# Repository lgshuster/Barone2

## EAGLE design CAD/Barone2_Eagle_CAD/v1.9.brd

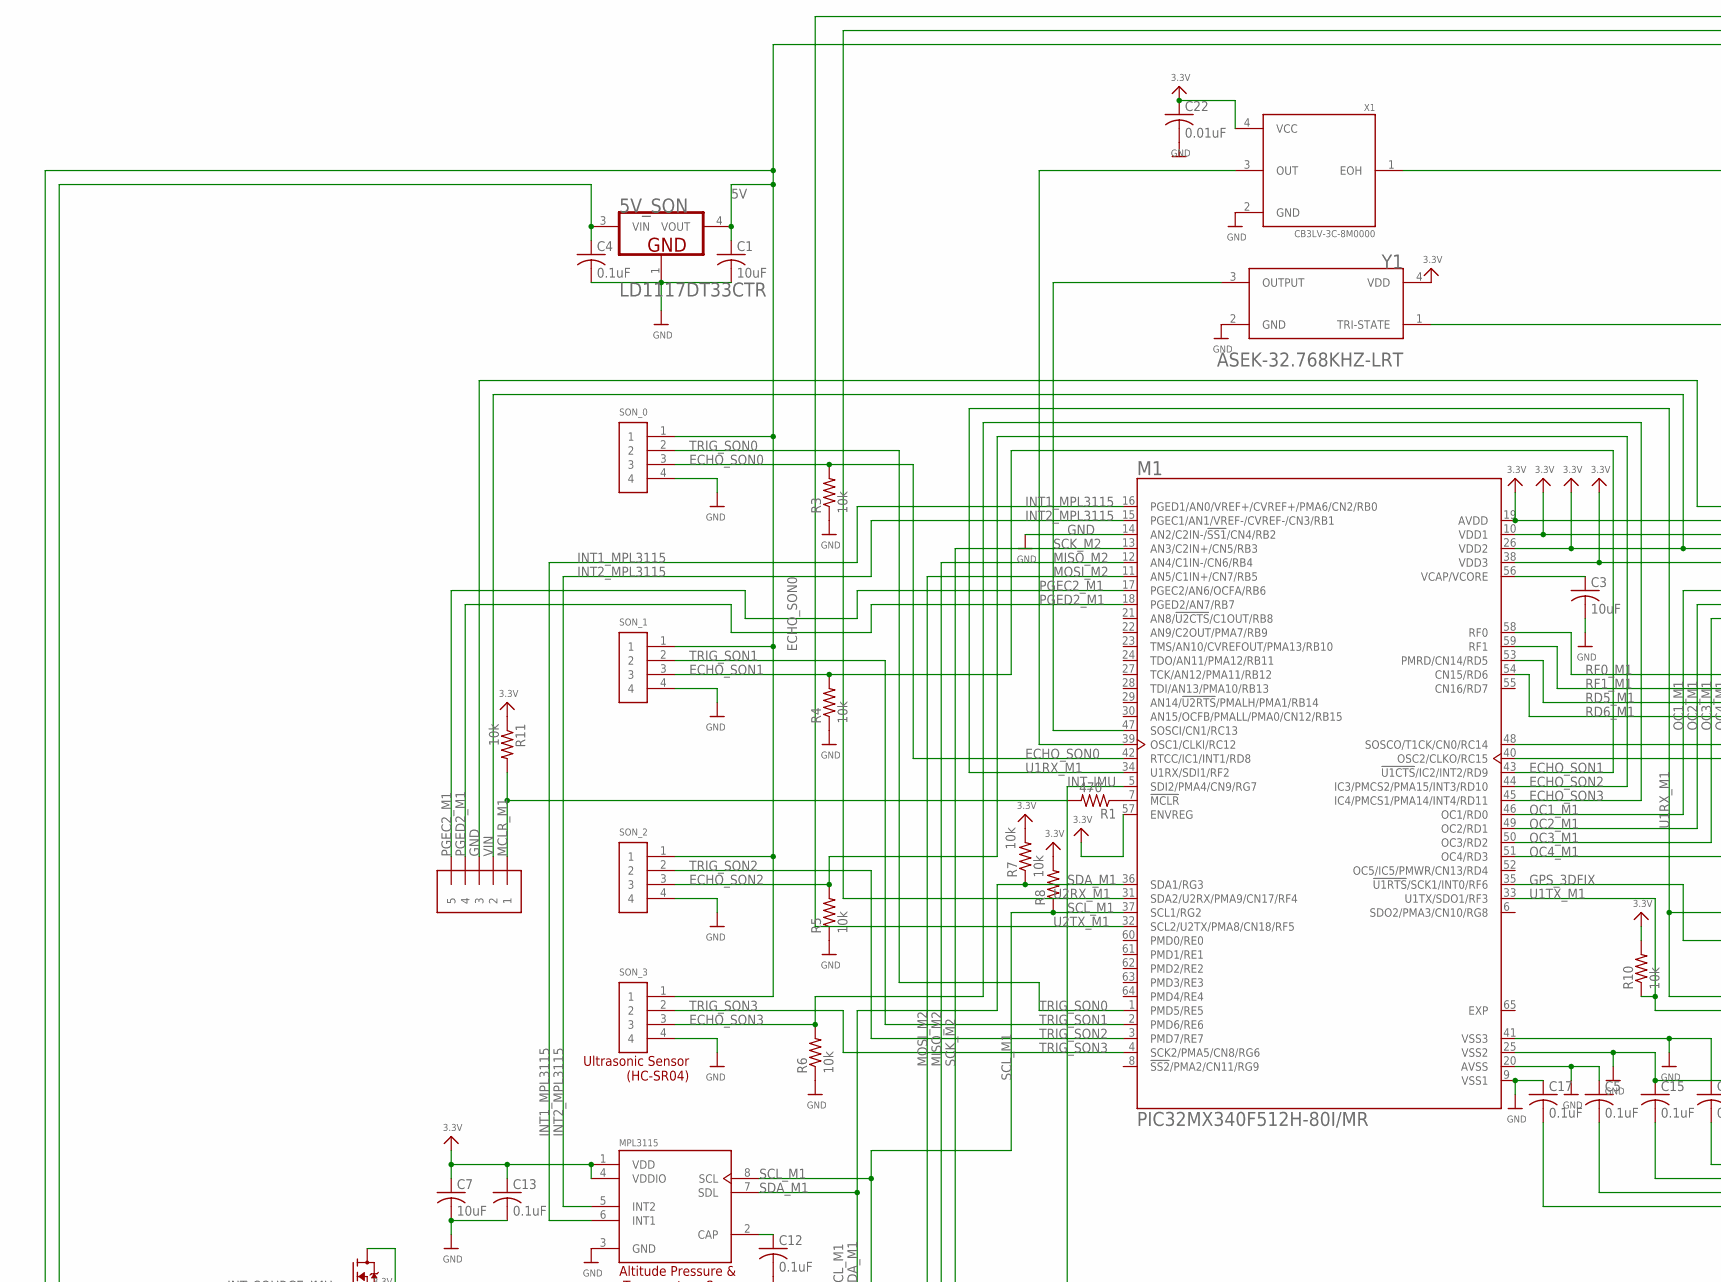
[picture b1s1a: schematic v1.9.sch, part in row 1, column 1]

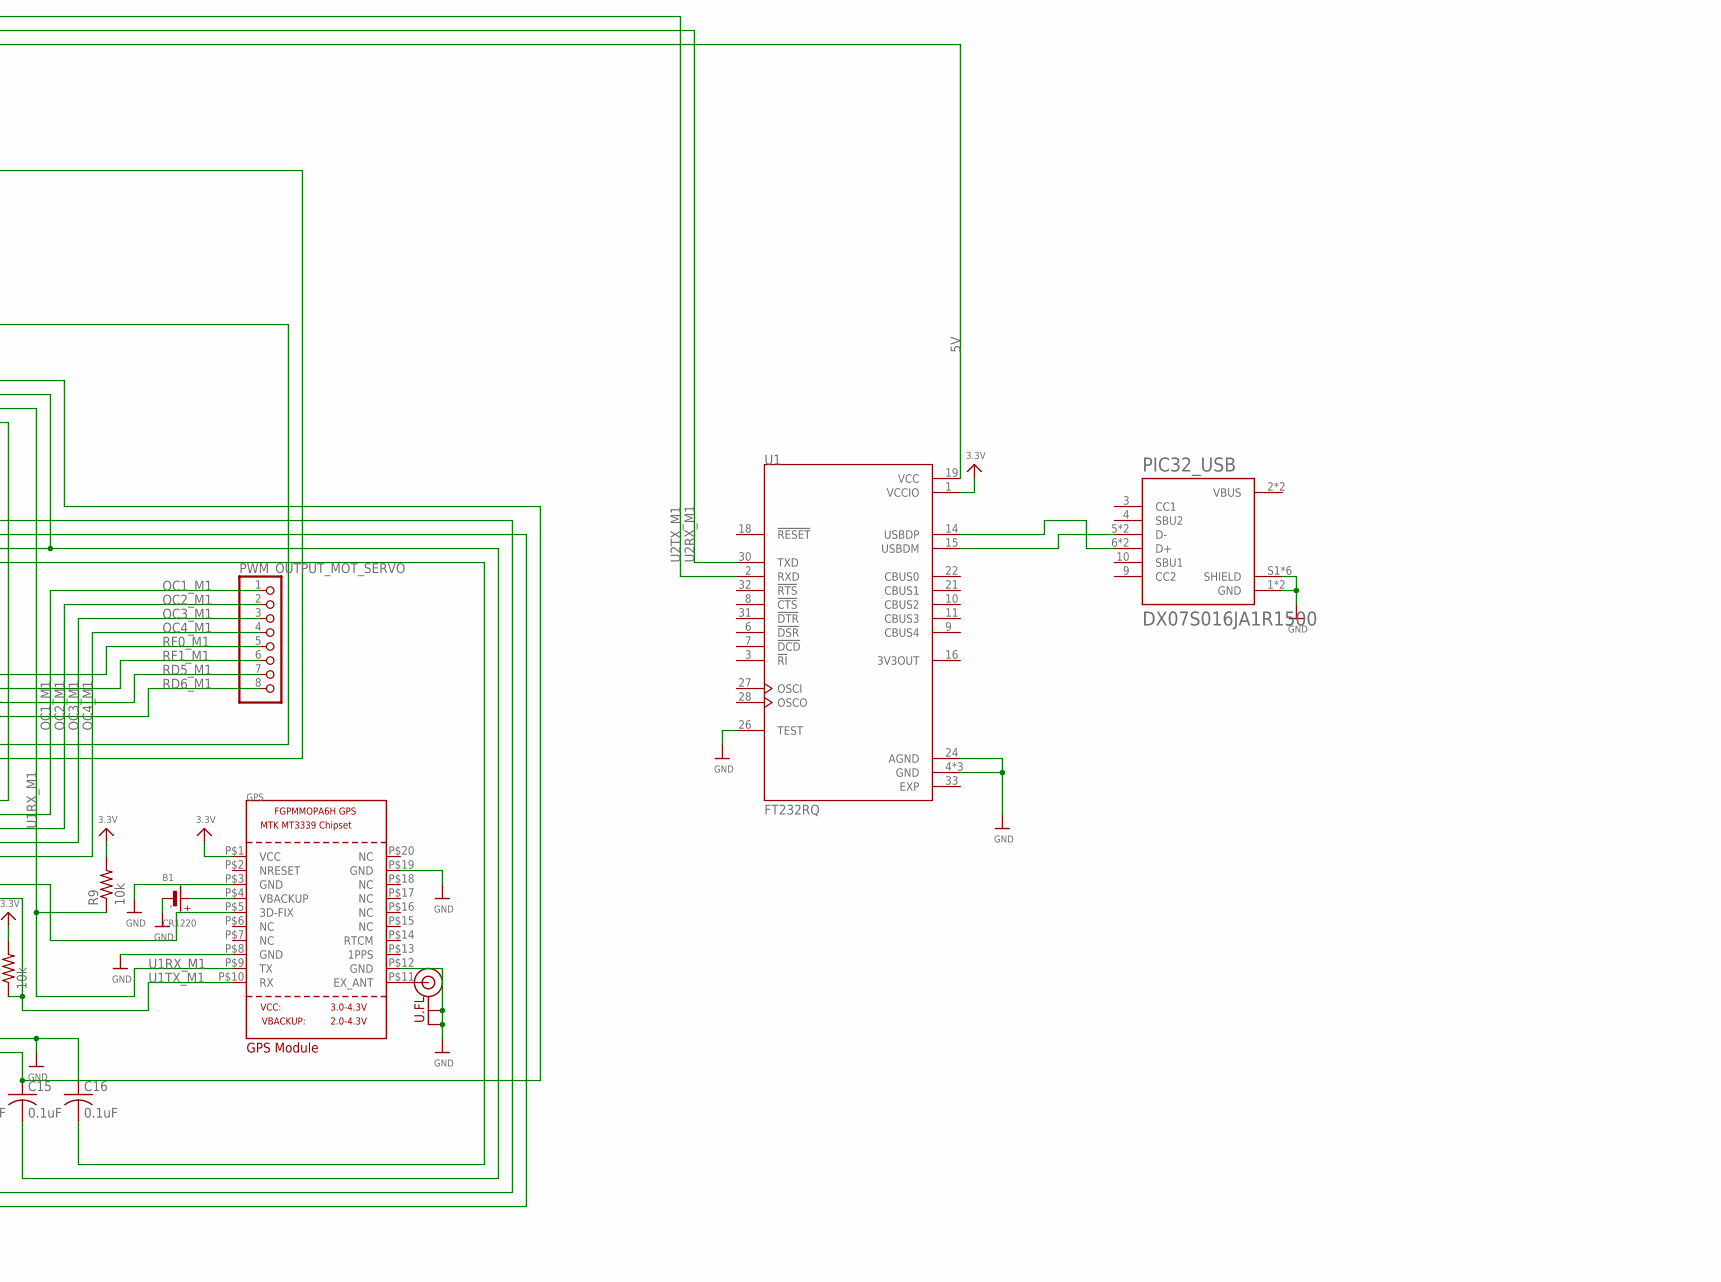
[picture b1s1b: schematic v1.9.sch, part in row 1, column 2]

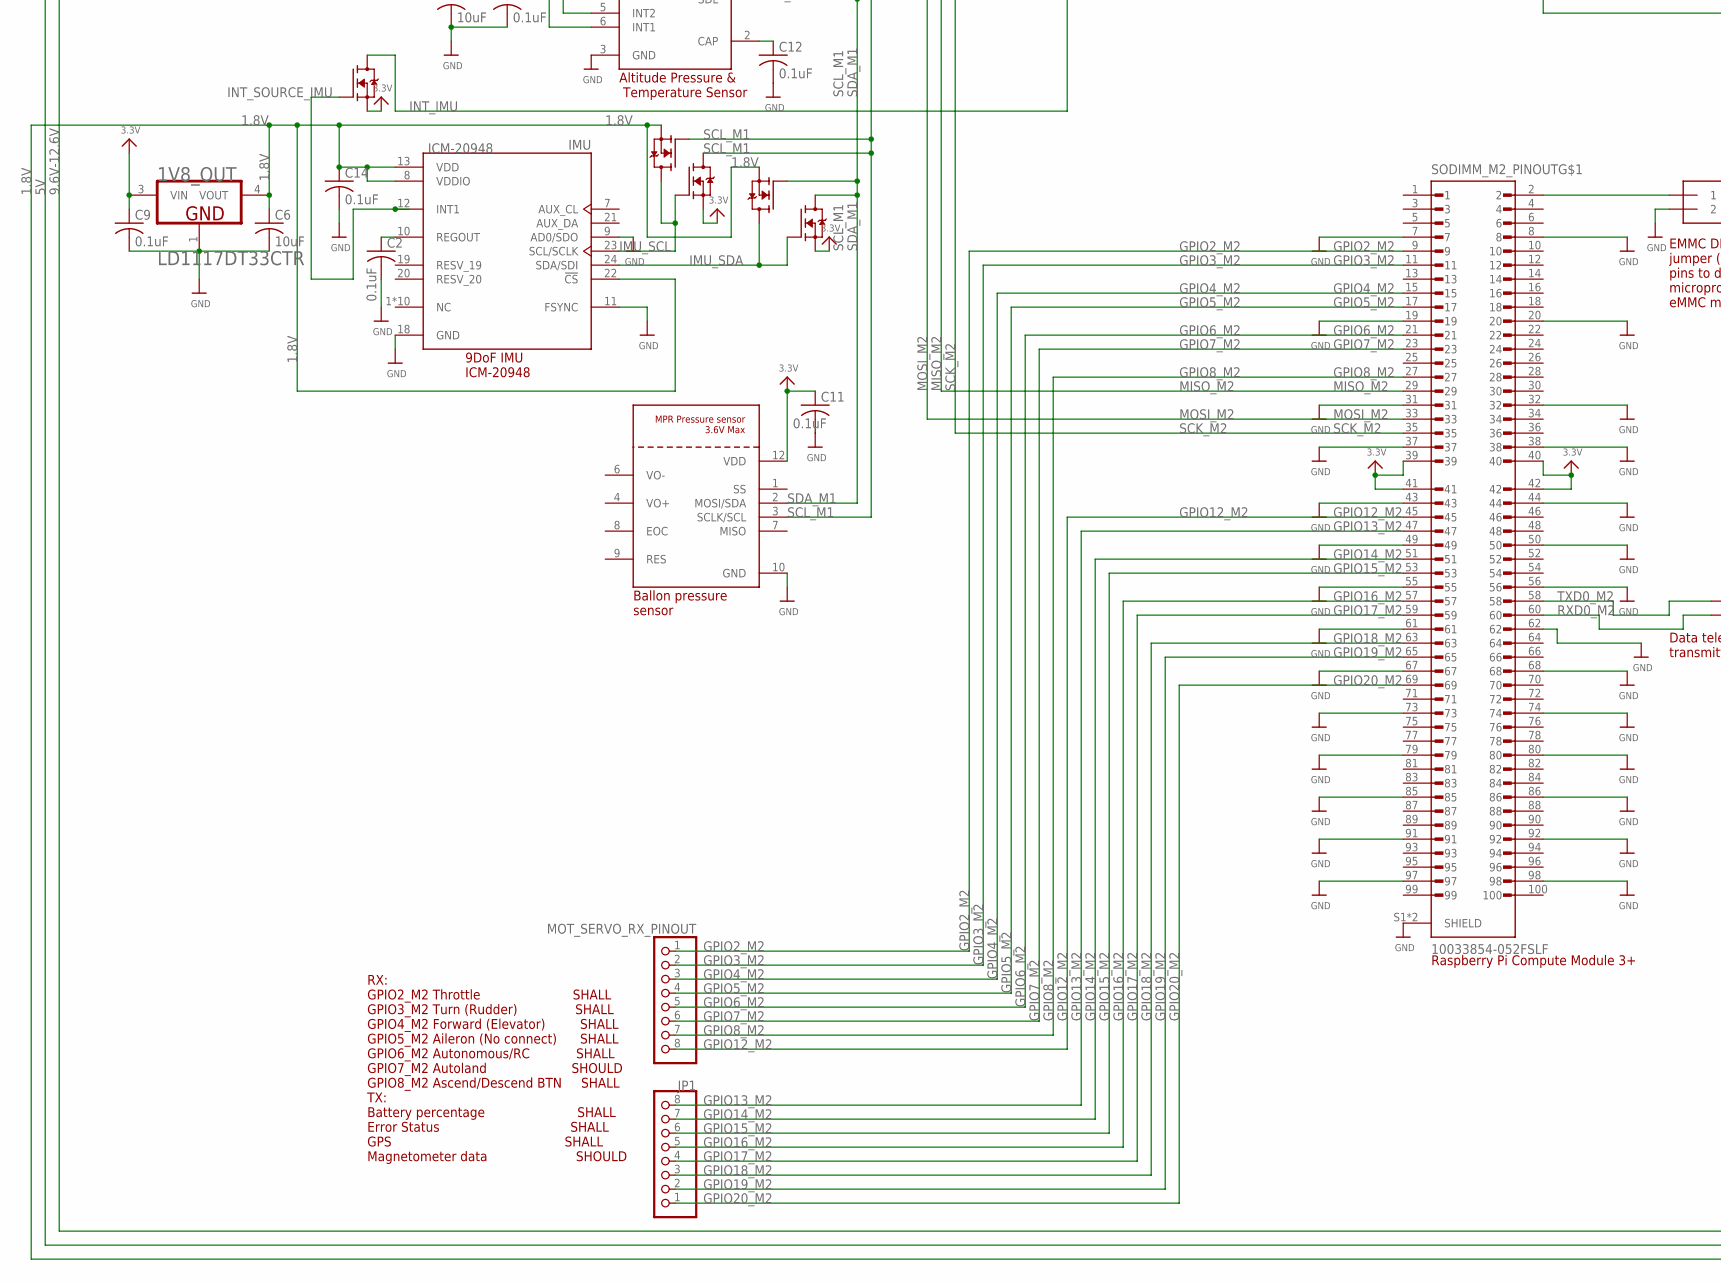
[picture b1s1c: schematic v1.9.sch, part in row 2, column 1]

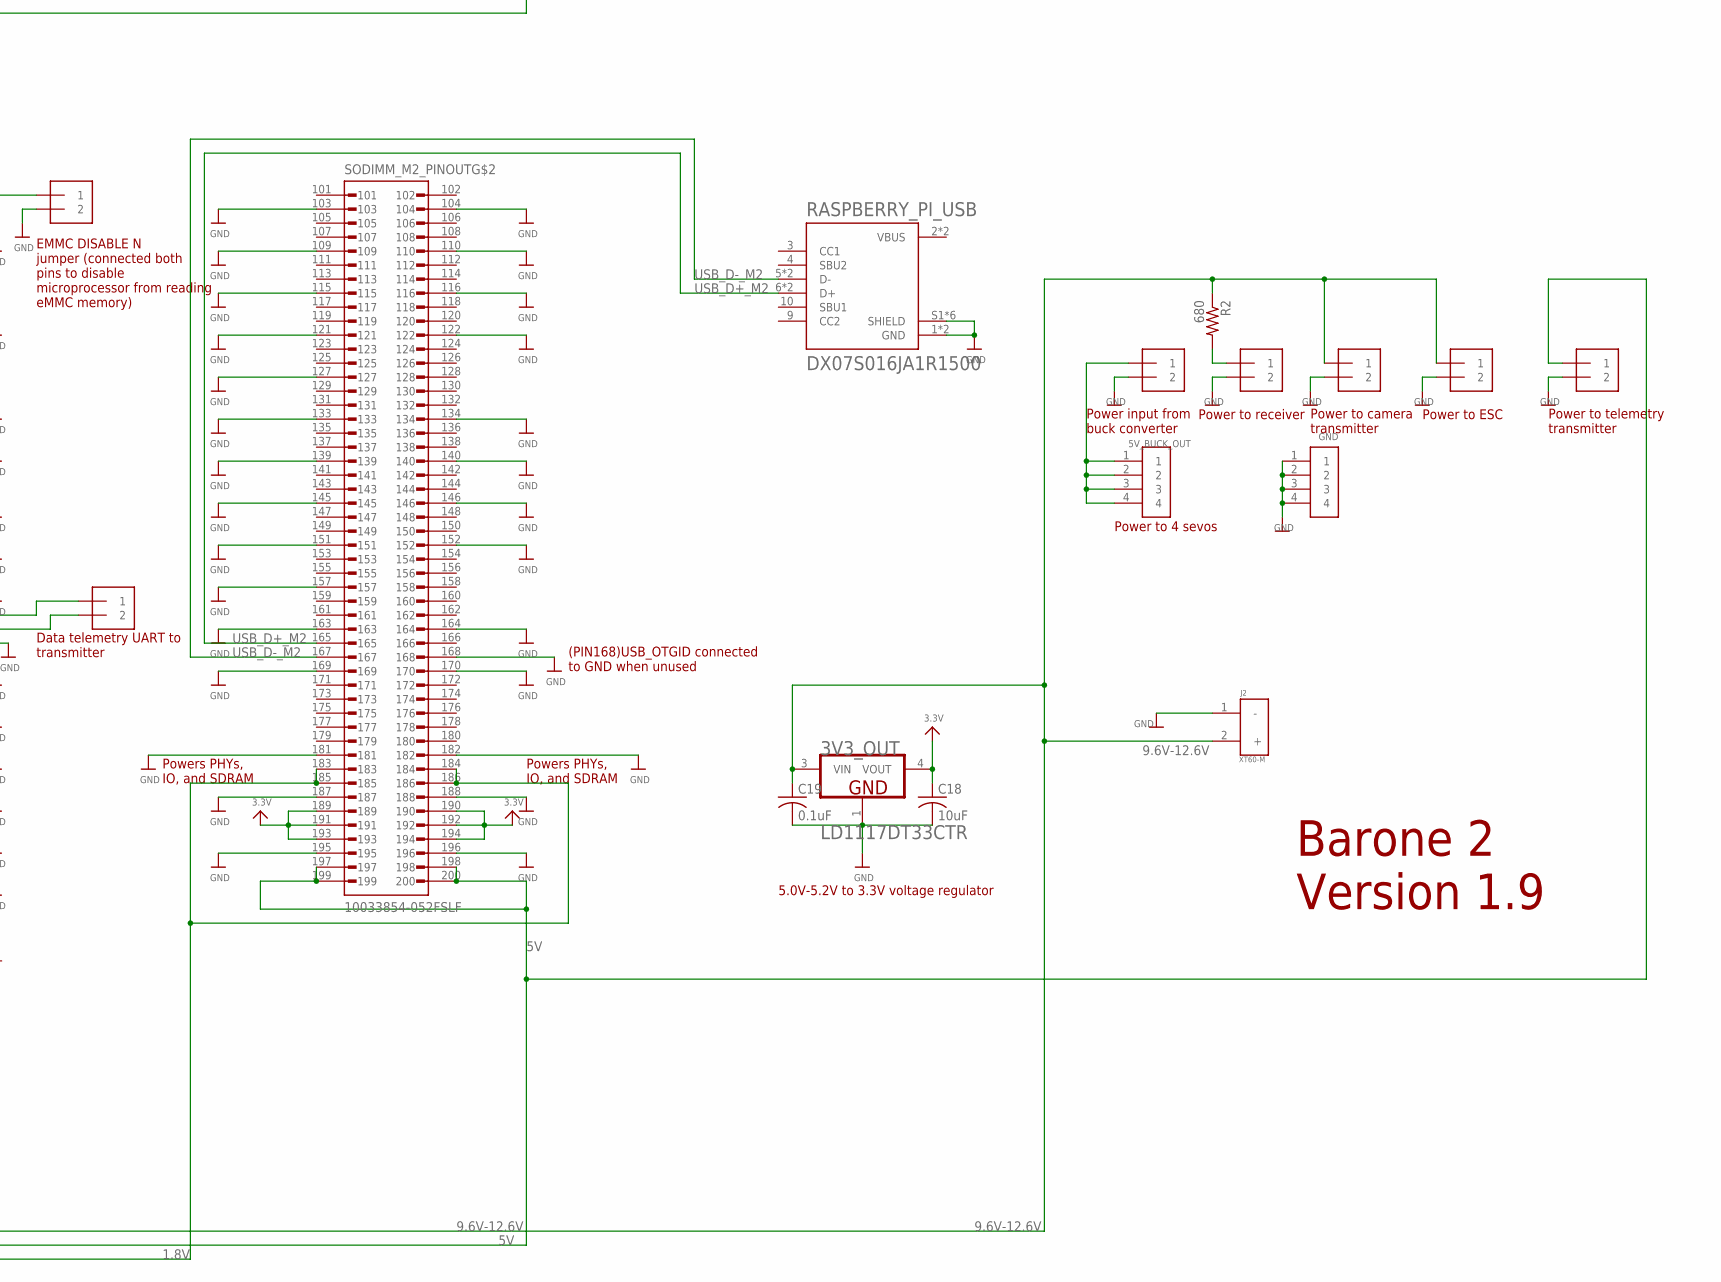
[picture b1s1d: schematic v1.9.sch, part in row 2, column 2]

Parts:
1V8_OUT, 3V3_OUT, 5V_SON: STMICROELECTRONICS_LD1117DT33CTRSTMICROELECTRONIC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; STMICROELECTRONICS_LD1117DT33CTR_2
5V_BUCK_IN: 1X2-3.5MM
5V_BUCK_OUT: 1X4-BIG; 1X04-BIG
B1: CR1220
C1, C3, C6, C7, C18: 10uF; C0805
C2, C4, C5, C9, C11, C12, C13, C14, C15, C16, C17, C19: 0.1uF; C0805
C22: 0.01uF; C0805
CAMERA_POWER: 1X2-3.5MM
EMMC_DISABLE_N: 1X2-3.5MM
ESC_POWER: 1X2-3.5MM
GND: 1X4-BIG; 1X04-BIG
GPS: GPS_FGPMMOPA6H; FGPMMOPA6H
ICSP: 1X5; 1X05-3.5MM
IMU: ICM-20948; QFN40P300X300X105-24N
INT_LLC_IMU: BSS138; SOT95P240X111-3N
J2: XT60-M; AMASS_XT60-M
JP1: PINHD-1X8CLEANBIG; 1X08-CLEANBIG
M1: PIC32MX340F512H-80I/MR; QFN50P900X900X100-65N
MOT_SERVO_RX_PINOUT: PINHD-1X8CLEANBIG; 1X08-CLEANBIG
MPL3115: MPL3115A2; PSON125P300X500X120-8N
MPR: MPR_SERIES_I2C_PRESSURE
PIC32_USB: DX07S016JA1R1500; JAE_DX07S016JA1R1500
PWM_OUTPUT_MOT_SERVO: PINHD-1X8CLEANBIG; 1X08-CLEANBIG
R1: 470; R0805W
R2: 680; R0805W
R3, R4, R5, R6, R7, R8, R9, R10, R11: 10k; R0805W
RASPBERRY_PI_USB: DX07S016JA1R1500; JAE_DX07S016JA1R1500
RC_RECEIVER_POWER: 1X2-3.5MM
SCL_IN_IMU: BSS138; SOT95P240X111-3N
SCL_OUT_IMU: BSS138; SOT95P240X111-3N
SDA_IN_IMU1: BSS138; SOT95P240X111-3N
SDA_OUT_IMU: BSS138; SOT95P240X111-3N
SODIMM_M2_PINOUT: 10033854-052FSLF; AMPHENOL_10033854-052FSLF
SON_0, SON_1, SON_2, SON_3: 1X4-BIG; 1X04-BIG
U1: FT232RQ; QFN50P500X500X90-33N
U.FL: U.FL
UART_M2, UART_M2_TX_POWER: 1X2-3.5MM
X1: CB3LV-3C-8M0000; OSCCC700X500X180-4N
Y1: ABRACON_ASEK-32_768KHZ-LRTABRACON_ASEK-32_768KHZ-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; ABRACON_ASEK-32_768KHZ-LRT_0

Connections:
1.8V: 1V8_OUT.4 (VOUT), C6.1, C14.1, IMU.8 (VDDIO), IMU.13 (VDD), IMU.22 (!CS), SCL_IN_IMU.2 (S), SDA_OUT_IMU.2 (S), SODIMM_M2_PINOUT.183, SODIMM_M2_PINOUT.184, SODIMM_M2_PINOUT.185, SODIMM_M2_PINOUT.186
5V: 5V_SON.4 (VOUT), C1.1, SODIMM_M2_PINOUT.197, SODIMM_M2_PINOUT.198, SODIMM_M2_PINOUT.199, SODIMM_M2_PINOUT.200, SON_0.1, SON_1.1, SON_2.1, SON_3.1, U1.19 (VCC), UART_M2_TX_POWER.1
9.6V-12.6V: 3V3_OUT.3 (VIN), 5V_SON.3 (VIN), C4.1, C19.1, CAMERA_POWER.1, ESC_POWER.1, J2.2 (+), R2.1
ECHO_SON0: M1.42 (RTCC/IC1/INT1/RD8), R3.2, SON_0.3
ECHO_SON1: M1.43 (!U1CTS!/IC2/INT2/RD9), R4.2, SON_1.3
ECHO_SON2: M1.44 (IC3/PMCS2/PMA15/INT3/RD10), R5.2, SON_2.3
ECHO_SON3: M1.45 (IC4/PMCS1/PMA14/INT4/RD11), R6.2, SON_3.3
EXP: M1.65 (EXP), U1.33 (EXP)
GND: 1V8_OUT.1 (GND), 3V3_OUT.1 (GND), 5V_BUCK_IN.2, 5V_SON.1 (GND), B1.-, C1.2, C2.2, C3.2, C4.2, C5.1, C6.2, C7.2, C9.2, C11.2, C12.2, C13.2, C14.2, C15.1, C16.1, C17.1, C18.2, C19.2, C22.2, CAMERA_POWER.2, EMMC_DISABLE_N.2, ESC_POWER.2, GND.1, GND.2, GND.3, GND.4, GPS.P$3 (GND), GPS.P$8 (GND), GPS.P$19 (GND), ICSP.3, IMU.9 (AD0/SDO), IMU.11 (FSYNC), IMU.18 (GND), J2.1 (-), M1.9 (VSS1), M1.14 (AN2/C2IN-/!SS1!/CN4/RB2), M1.20 (AVSS), M1.25 (VSS2), M1.41 (VSS3), MPL3115.3 (GND), MPR.10 (GND), PIC32_USB.1 (GND), PIC32_USB.12 (GND), PIC32_USB.S1 (SHIELD), PIC32_USB.S2 (SHIELD), PIC32_USB.S3 (SHIELD), PIC32_USB.S4 (SHIELD), PIC32_USB.S5 (SHIELD), PIC32_USB.S6 (SHIELD), R3.1, R4.1, R5.1, R6.1, RASPBERRY_PI_USB.1 (GND), RASPBERRY_PI_USB.12 (GND), RASPBERRY_PI_USB.S1 (SHIELD), RASPBERRY_PI_USB.S2 (SHIELD), RASPBERRY_PI_USB.S3 (SHIELD), RASPBERRY_PI_USB.S4 (SHIELD), RASPBERRY_PI_USB.S5 (SHIELD), RASPBERRY_PI_USB.S6 (SHIELD), RC_RECEIVER_POWER.2, SODIMM_M2_PINOUT.7, SODIMM_M2_PINOUT.8, SODIMM_M2_PINOUT.19, SODIMM_M2_PINOUT.20, SODIMM_M2_PINOUT.31, SODIMM_M2_PINOUT.32, SODIMM_M2_PINOUT.37, SODIMM_M2_PINOUT.38, SODIMM_M2_PINOUT.43, SODIMM_M2_PINOUT.44, SODIMM_M2_PINOUT.49, SODIMM_M2_PINOUT.50, SODIMM_M2_PINOUT.55, SODIMM_M2_PINOUT.56, SODIMM_M2_PINOUT.61, SODIMM_M2_PINOUT.62, SODIMM_M2_PINOUT.67, SODIMM_M2_PINOUT.68, SODIMM_M2_PINOUT.73, SODIMM_M2_PINOUT.74, SODIMM_M2_PINOUT.79, SODIMM_M2_PINOUT.80, SODIMM_M2_PINOUT.85, SODIMM_M2_PINOUT.86, SODIMM_M2_PINOUT.91, SODIMM_M2_PINOUT.92, SODIMM_M2_PINOUT.97, SODIMM_M2_PINOUT.98, SODIMM_M2_PINOUT.103, SODIMM_M2_PINOUT.104, SODIMM_M2_PINOUT.109, SODIMM_M2_PINOUT.110, SODIMM_M2_PINOUT.115, SODIMM_M2_PINOUT.116, SODIMM_M2_PINOUT.121, SODIMM_M2_PINOUT.122, SODIMM_M2_PINOUT.127, SODIMM_M2_PINOUT.133, SODIMM_M2_PINOUT.134, SODIMM_M2_PINOUT.139, SODIMM_M2_PINOUT.140, SODIMM_M2_PINOUT.145, SODIMM_M2_PINOUT.146, SODIMM_M2_PINOUT.151, SODIMM_M2_PINOUT.152, SODIMM_M2_PINOUT.157, SODIMM_M2_PINOUT.163, SODIMM_M2_PINOUT.164, SODIMM_M2_PINOUT.168, SODIMM_M2_PINOUT.169, SODIMM_M2_PINOUT.170, SODIMM_M2_PINOUT.181, SODIMM_M2_PINOUT.182, SODIMM_M2_PINOUT.187, SODIMM_M2_PINOUT.188, SODIMM_M2_PINOUT.195, SODIMM_M2_PINOUT.196, SODIMM_M2_PINOUT.S1 (SHIELD), SODIMM_M2_PINOUT.S2 (SHIELD), SON_0.4, SON_1.4, SON_2.4, SON_3.4, U1.4 (GND), U1.17 (GND), U1.20 (GND), U1.24 (AGND), U1.26 (TEST)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
GPIO2_M2: MOT_SERVO_RX_PINOUT.1, SODIMM_M2_PINOUT.9
GPIO3_M2: MOT_SERVO_RX_PINOUT.2, SODIMM_M2_PINOUT.11
GPIO4_M2: MOT_SERVO_RX_PINOUT.3, SODIMM_M2_PINOUT.15
GPIO5_M2: MOT_SERVO_RX_PINOUT.4, SODIMM_M2_PINOUT.17
GPIO6_M2: MOT_SERVO_RX_PINOUT.5, SODIMM_M2_PINOUT.21
GPIO7_M2: MOT_SERVO_RX_PINOUT.6, SODIMM_M2_PINOUT.23
GPIO8_M2: MOT_SERVO_RX_PINOUT.7, SODIMM_M2_PINOUT.27
GPIO12_M2: MOT_SERVO_RX_PINOUT.8, SODIMM_M2_PINOUT.45
GPIO13_M2: JP1.8, SODIMM_M2_PINOUT.47
GPIO14_M2: JP1.7, SODIMM_M2_PINOUT.51
GPIO15_M2: JP1.6, SODIMM_M2_PINOUT.53
GPIO16_M2: JP1.5, SODIMM_M2_PINOUT.57
GPIO17_M2: JP1.4, SODIMM_M2_PINOUT.59
GPIO18_M2: JP1.3, SODIMM_M2_PINOUT.63
GPIO19_M2: JP1.2, SODIMM_M2_PINOUT.65
GPIO20_M2: JP1.1, SODIMM_M2_PINOUT.69
GPS_3DFIX: GPS.P$5 (3D-FIX), M1.35 (!U1RTS!/SCK1/INT0/RF6)
IMU_SCL: IMU.23 (SCL/SCLK), SCL_IN_IMU.3 (D), SCL_OUT_IMU.1 (G)
IMU_SDA: IMU.24 (SDA/SDI), SDA_IN_IMU1.1 (G), SDA_OUT_IMU.3 (D)
INT1_MPL3115: M1.16 (PGED1/AN0/VREF+/CVREF+/PMA6/CN2/RB0), MPL3115.6 (INT1)
INT2_MPL3115: M1.15 (PGEC1/AN1/VREF-/CVREF-/CN3/RB1), MPL3115.5 (INT2)
INT_IMU: INT_LLC_IMU.3 (D), M1.5 (SDI2/PMA4/CN9/RG7)
INT_SOURCE_IMU: IMU.12 (INT1), INT_LLC_IMU.1 (G)
MCLR_M1: ICSP.1, R1.2, R11.2
MISO_M2: M1.12 (AN4/C1IN-/CN6/RB4), SODIMM_M2_PINOUT.29
MOSI_M2: M1.11 (AN5/C1IN+/CN7/RB5), SODIMM_M2_PINOUT.33
unnamed: GPS.P$12 (GND), U.FL.P$1 (GND), U.FL.P$2 (GND)
unnamed: GPS.P$11 (EX_ANT), U.FL.P$3 (SIGNAL)
unnamed: EMMC_DISABLE_N.1, SODIMM_M2_PINOUT.2
unnamed: 5V_BUCK_IN.1, 5V_BUCK_OUT.1, 5V_BUCK_OUT.2, 5V_BUCK_OUT.3, 5V_BUCK_OUT.4
unnamed: M1.40 (OSC2/CLKO/RC15), X1.1 (EOH)
unnamed: M1.39 (OSC1/CLKI/RC12), X1.3 (OUT)
unnamed: M1.48 (SOSCO/T1CK/CN0/RC14), Y1.1 (TRI-STATE)
unnamed: M1.47 (SOSCI/CN1/RC13), Y1.3 (OUTPUT)
unnamed: C12.1, MPL3115.2 (CAP)
unnamed: M1.7 (!MCLR), R1.1
unnamed: R2.2, RC_RECEIVER_POWER.1
unnamed: PIC32_USB.5 (D-), PIC32_USB.8 (D-), U1.15 (USBDM)
unnamed: PIC32_USB.6 (D+), PIC32_USB.7 (D+), U1.14 (USBDP)
unnamed: B1.+$1 (+), B1.+$2 (+), GPS.P$4 (VBACKUP)
unnamed: C2.1, IMU.10 (REGOUT)
OC1_M1: M1.46 (OC1/RD0), PWM_OUTPUT_MOT_SERVO.1
OC2_M1: M1.49 (OC2/RD1), PWM_OUTPUT_MOT_SERVO.2
OC3_M1: M1.50 (OC3/RD2), PWM_OUTPUT_MOT_SERVO.3
OC4_M1: M1.51 (OC4/RD3), PWM_OUTPUT_MOT_SERVO.4
PGEC2_M1: ICSP.5, M1.17 (PGEC2/AN6/OCFA/RB6)
PGED2_M1: ICSP.4, M1.18 (PGED2/AN7/RB7)
RD5_M1: M1.53 (PMRD/CN14/RD5), PWM_OUTPUT_MOT_SERVO.7
RD6_M1: M1.54 (CN15/RD6), PWM_OUTPUT_MOT_SERVO.8
RF0_M1: M1.58 (RF0), PWM_OUTPUT_MOT_SERVO.5
RF1_M1: M1.59 (RF1), PWM_OUTPUT_MOT_SERVO.6
RXD0_M2: SODIMM_M2_PINOUT.60, UART_M2.2
SCK_M2: M1.13 (AN3/C2IN+/CN5/RB3), SODIMM_M2_PINOUT.35
SCL_M1: M1.37 (SCL1/RG2), MPL3115.8 (SCL), MPR.3 (SCLK/SCL), R8.1, SCL_IN_IMU.1 (G), SCL_OUT_IMU.3 (D)
SDA_M1: M1.36 (SDA1/RG3), MPL3115.7 (SDL), MPR.2 (MOSI/SDA), R7.1, SDA_IN_IMU1.3 (D), SDA_OUT_IMU.1 (G)
TRIG_SON0: M1.1 (PMD5/RE5), SON_0.2
TRIG_SON1: M1.2 (PMD6/RE6), SON_1.2
TRIG_SON2: M1.3 (PMD7/RE7), SON_2.2
TRIG_SON3: M1.4 (SCK2/PMA5/CN8/RG6), SON_3.2
TXD0_M2: SODIMM_M2_PINOUT.58, UART_M2.1
U1RX_M1: GPS.P$9 (TX), M1.34 (U1RX/SDI1/RF2), R9.1
U1TX_M1: GPS.P$10 (RX), M1.33 (U1TX/SDO1/RF3), R10.1
U2RX_M1: M1.31 (SDA2/U2RX/PMA9/CN17/RF4), U1.30 (TXD)
U2TX_M1: M1.32 (SCL2/U2TX/PMA8/CN18/RF5), U1.2 (RXD)
USB_D+_M2: RASPBERRY_PI_USB.6 (D+), RASPBERRY_PI_USB.7 (D+), SODIMM_M2_PINOUT.165
USB_D-_M2: RASPBERRY_PI_USB.5 (D-), RASPBERRY_PI_USB.8 (D-), SODIMM_M2_PINOUT.167
VBUS: PIC32_USB.2 (VBUS), PIC32_USB.11 (VBUS), RASPBERRY_PI_USB.2 (VBUS), RASPBERRY_PI_USB.11 (VBUS)
VCAP_VCORE_M1: C3.1, M1.56 (VCAP/VCORE)
VIN: 1V8_OUT.3 (VIN), 3V3_OUT.4 (VOUT), C5.2, C7.1, C9.1, C11.1, C13.1, C15.2, C16.2, C17.2, C18.1, C22.1, GPS.P$1 (VCC), ICSP.2, INT_LLC_IMU.2 (S), M1.10 (VDD1), M1.19 (AVDD), M1.26 (VDD2), M1.38 (VDD3), M1.57 (ENVREG), MPL3115.1 (VDD), MPL3115.4 (VDDIO), MPR.12 (VDD), R7.2, R8.2, R9.2, R10.2, R11.1, SCL_OUT_IMU.2 (S), SDA_IN_IMU1.2 (S), SODIMM_M2_PINOUT.39, SODIMM_M2_PINOUT.40, SODIMM_M2_PINOUT.41, SODIMM_M2_PINOUT.42, SODIMM_M2_PINOUT.189, SODIMM_M2_PINOUT.190, SODIMM_M2_PINOUT.191, SODIMM_M2_PINOUT.192, SODIMM_M2_PINOUT.193, SODIMM_M2_PINOUT.194, U1.1 (VCCIO), X1.4 (VCC), Y1.4 (VDD)

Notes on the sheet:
9DoF IMU ICM-20948
Ultrasonic Sensor (HC-SR04)
GPS Module
5.0V-5.2V to 3.3V voltage regulator
Altitude Pressure & Temperature Sensor
Raspberry Pi Compute Module 3+
U.FL
Barone 2 Version 1.9
Ballon pressure sensor
Powers PHYs, IO, and SDRAM
(PIN168)USB_OTGID connected to GND when unused
Power to 4 sevos
RX: GPIO2_M2 Throttle SHALL GPIO3_M2 Turn (Rudder) SHALL GPIO4_M2 Forward (Elevator) SHALL GPIO5_M2 Aileron (No connect) SHALL GPIO6_M2 Autonomous/RC SHALL GPIO7_M2 Autoland SHOULD GPIO8_M2 Ascend/Descend BTN SHALL TX: Battery percentage SHALL Error Status SHALL GPS SHALL Magnetometer data SHOULD
Power to receiver
Power to camera transmitter
EMMC DISABLE N jumper (connected both pins to disable microprocessor from reading eMMC memory)
Data telemetry UART to transmitter
Power to ESC
Power input from buck converter
Power to telemetry transmitter

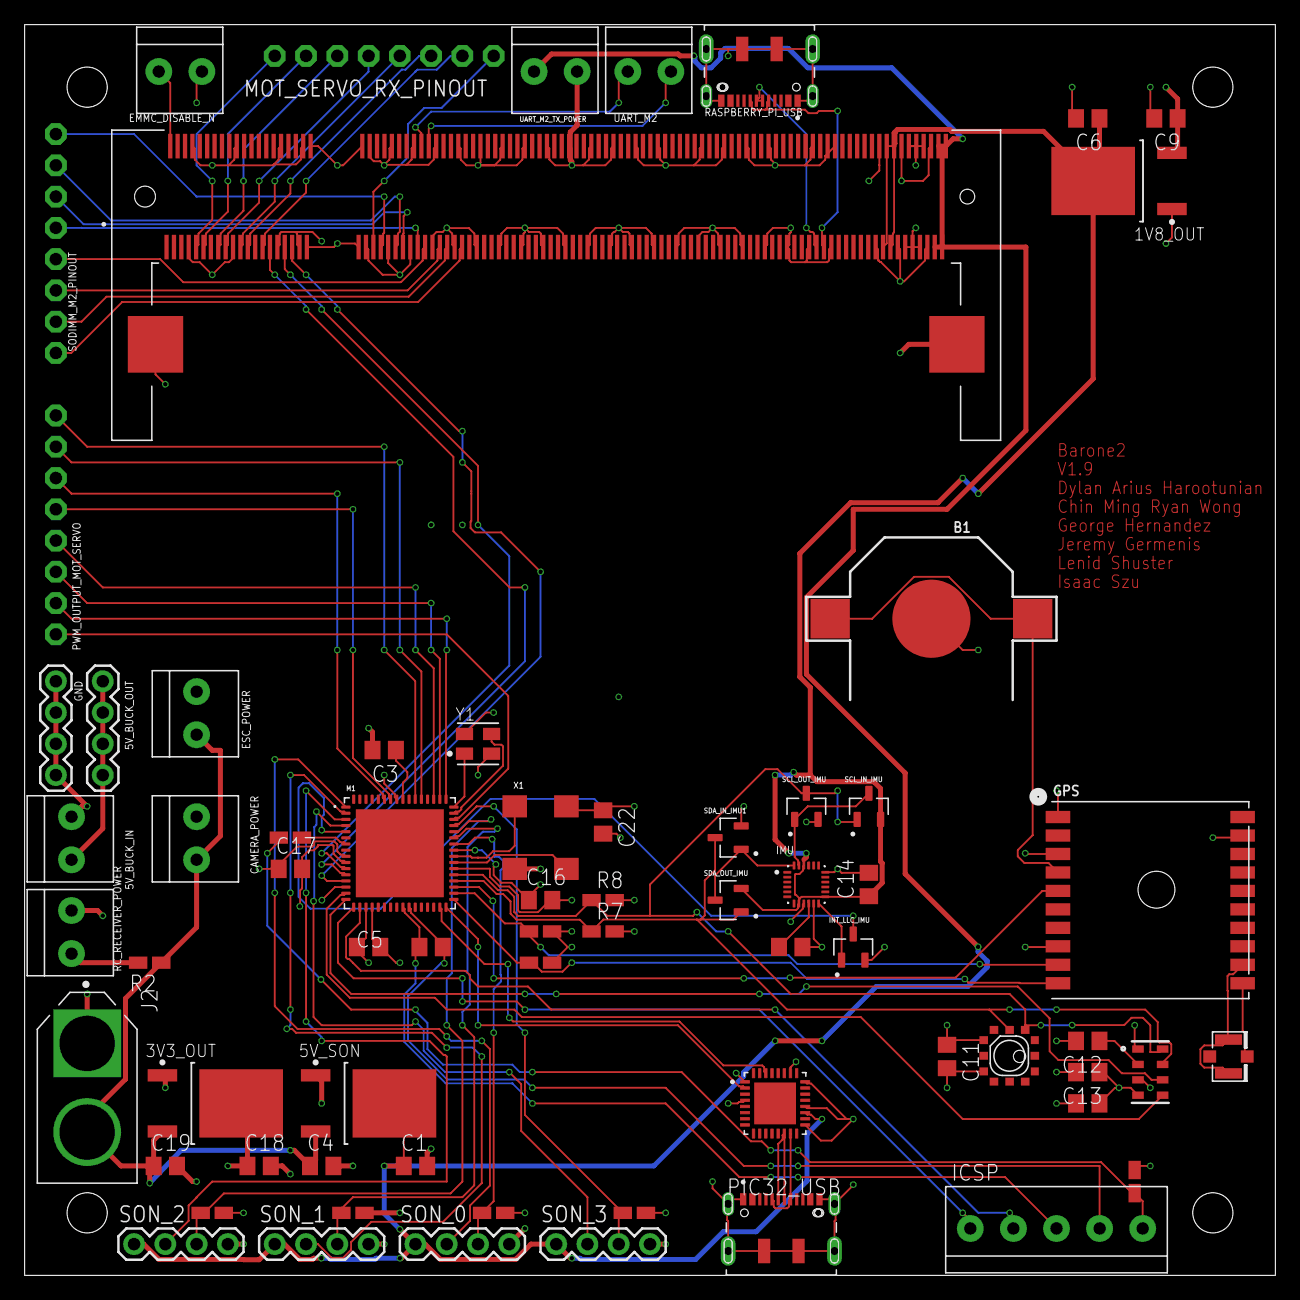
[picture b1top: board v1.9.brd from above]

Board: 4 copper layers, 101.6 x 101.6 mm, 68 parts (0 on the bottom side), 78 nets.

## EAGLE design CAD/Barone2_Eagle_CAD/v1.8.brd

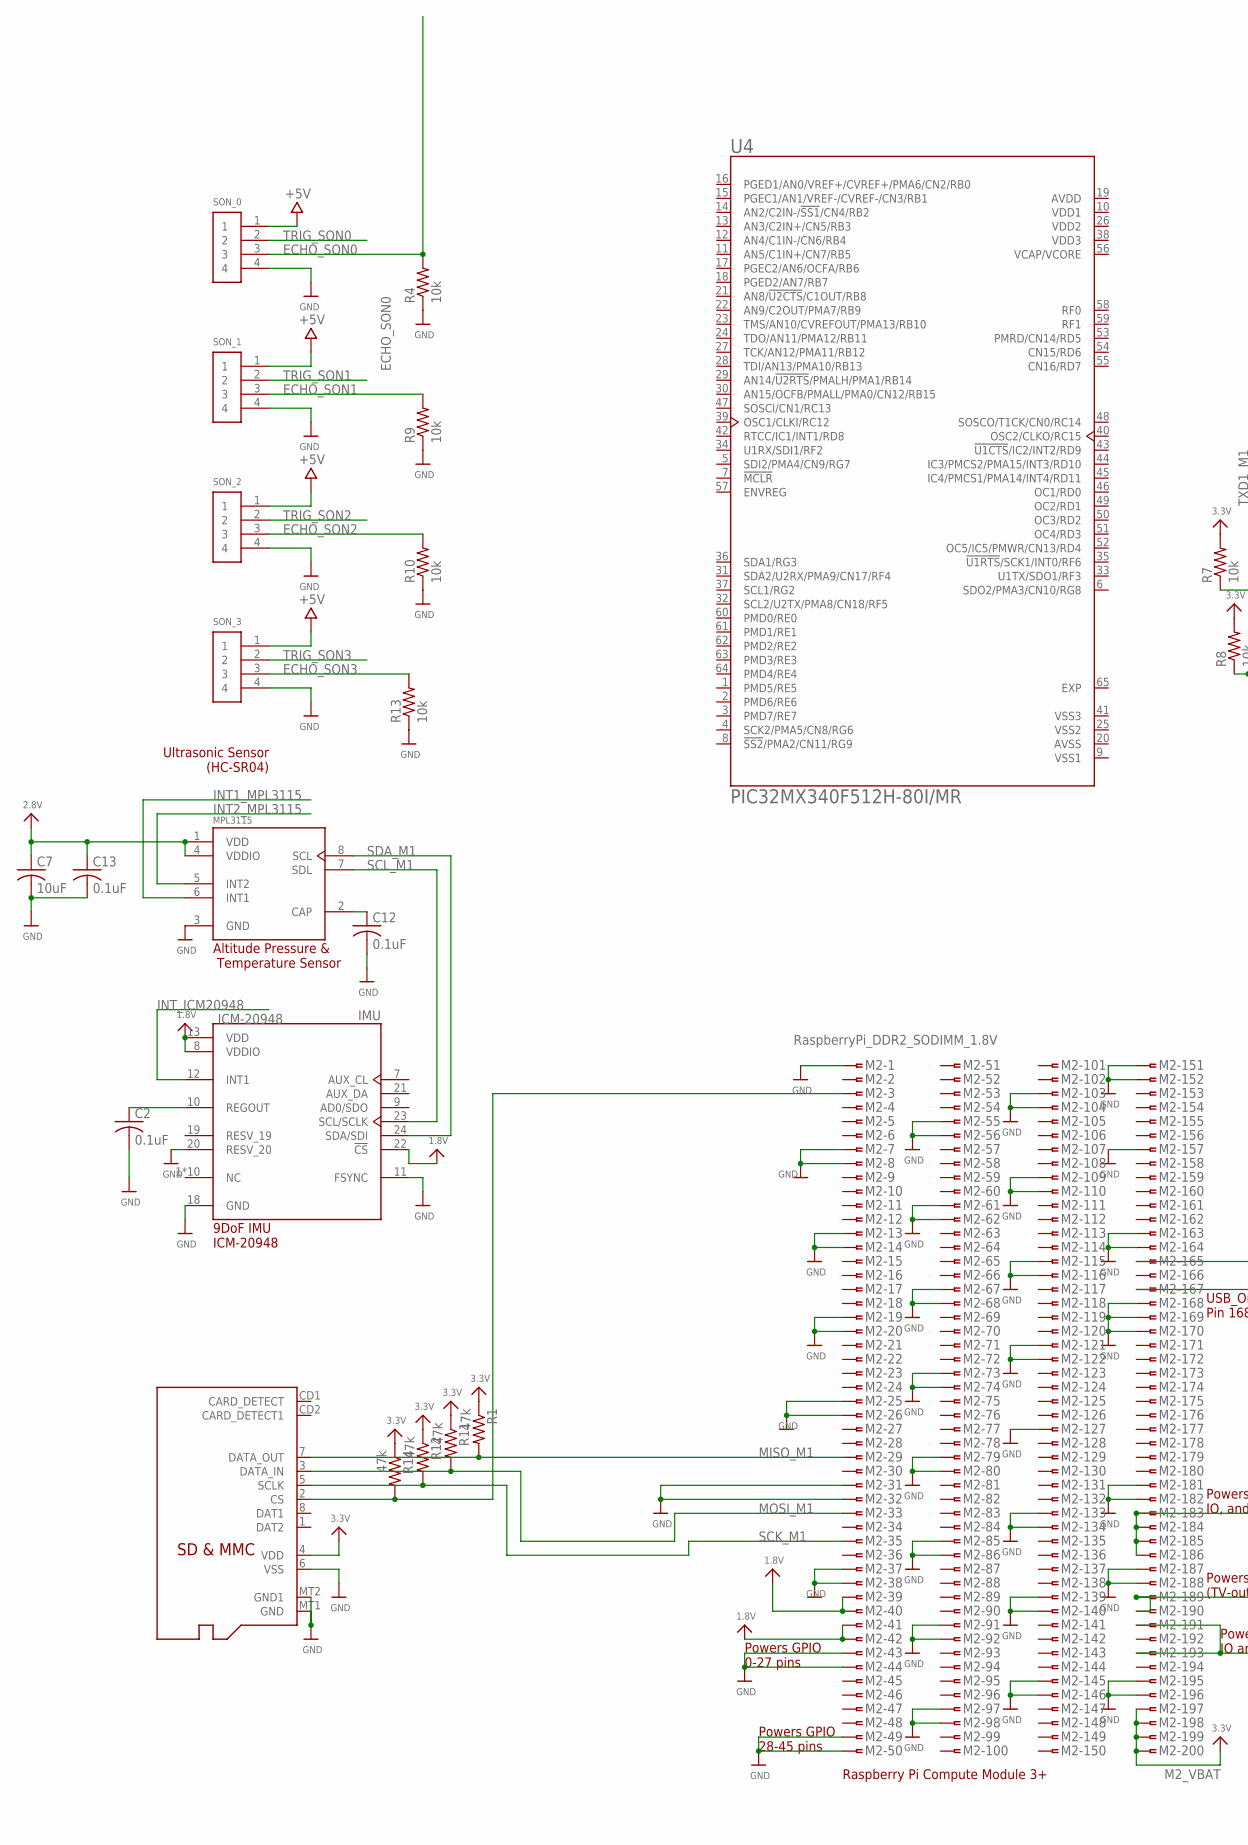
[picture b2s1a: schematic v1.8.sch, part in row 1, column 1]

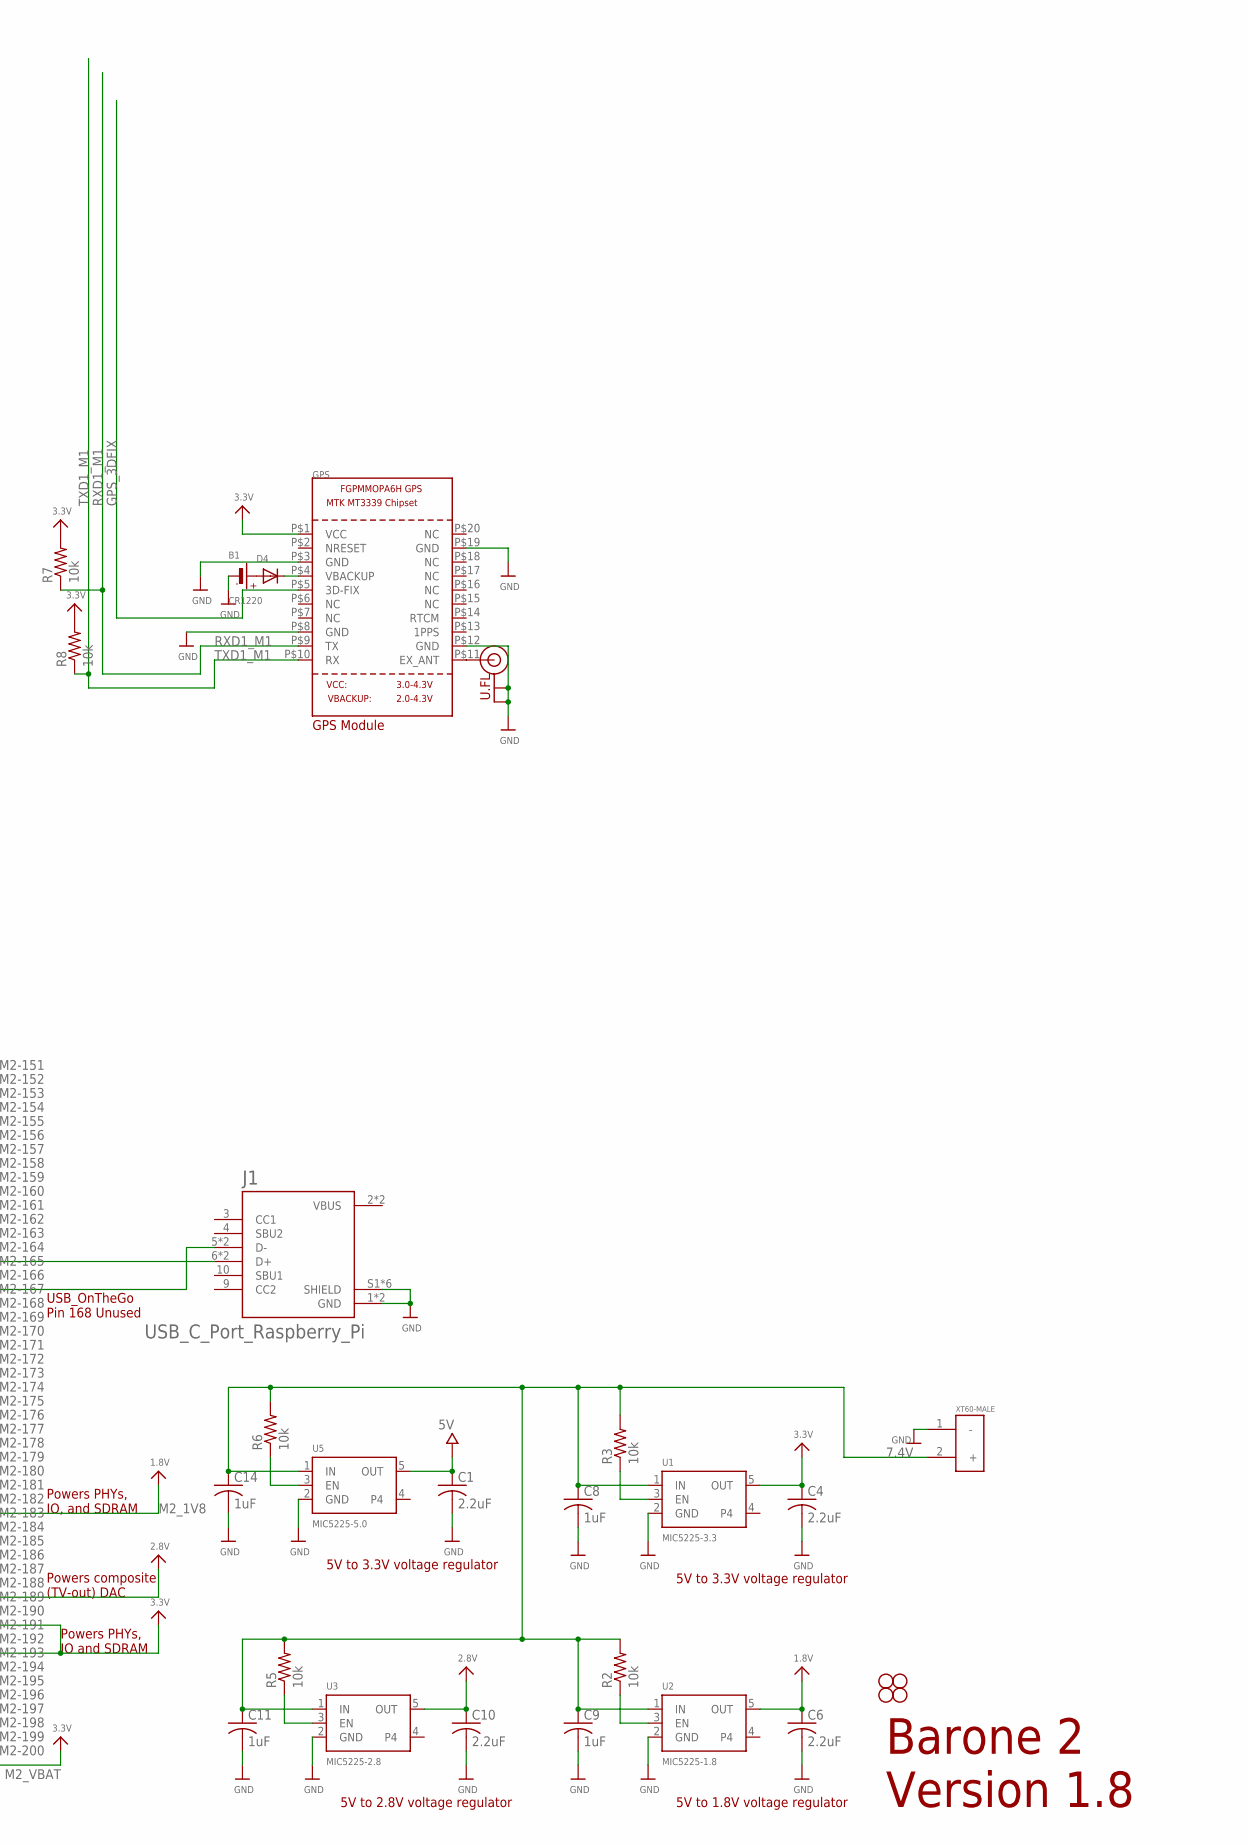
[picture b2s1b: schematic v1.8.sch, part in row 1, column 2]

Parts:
B1: CR1220
C1, C4, C6, C10: 2.2uF; C0805
C2, C12, C13: 0.1uF; C0805
C7: 10uF; C0805
C8, C9, C11, C14: 1uF; C0805
D4: DIODESOD-323F; SOD-323F
GPS: GPS_FGPMMOPA6H; FGPMMOPA6H
H1, H2, H3, H4: STAND-OFF
IMU: ICM-20948; QFN40P300X300X105-24N
J1: USB_C_Port_Raspberry_Pi; JAE_DX07S016JA1R1500
M2: RaspberryPi_DDR2_SODIMM_1.8V; SLOT-1376408-1_1.8V
MPL3115: MPL3115A2; PSON125P300X500X120-8N
R1, R11, R12, R14: 47k; R0805W
R2, R3, R4, R5, R6, R7, R8, R9, R10, R13: 10k; R0805W
SON_0, SON_1, SON_2, SON_3: 1X4-BIG; 1X04-BIG
U1: MIC5225-3.3; SOT23-5
U2: MIC5225-1.8; SOT23-5
U3: MIC5225-2.8; SOT23-5
U4: PIC32MX340F512H-80I/MR; QFN50P900X900X100-65N
U5: MIC5225-5.0; SOT23-5
U$6: MICROSD
U.FL: U.FL
XT60-MALE: XT60-M; AMASS_XT60-M

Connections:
7.4V: C8.1, C9.1, C11.1, C14.1, R2.2, R3.2, R5.2, R6.2, U1.1 (IN), U2.1 (IN), U3.1 (IN), U5.1 (IN), XT60-MALE.2 (+)
+5V: SON_0.1, SON_1.1, SON_2.1, SON_3.1
AVDD: U4.19 (AVDD)
AVSS: U4.20 (AVSS)
ECHO_SON0: R4.2, SON_0.3
ECHO_SON1: R9.2, SON_1.3
ECHO_SON2: R10.2, SON_2.3
ECHO_SON3: R13.2, SON_3.3
EXP: U4.65 (EXP)
GND: B1.-, C1.2, C2.2, C4.2, C6.2, C7.2, C8.2, C9.2, C10.2, C11.2, C12.2, C13.2, C14.2, GPS.P$3 (GND), GPS.P$8 (GND), GPS.P$19 (GND), IMU.11 (FSYNC), IMU.18 (GND), IMU.20 (RESV_20), J1.1 (GND), J1.12 (GND), J1.S1 (SHIELD), J1.S2 (SHIELD), J1.S3 (SHIELD), J1.S4 (SHIELD), J1.S5 (SHIELD), J1.S6 (SHIELD), M2.1, M2.7, M2.8, M2.13, M2.14, M2.19, M2.20, M2.25, M2.26, M2.31, M2.32, M2.37, M2.38, M2.43, M2.44, M2.49, M2.50, M2.55, M2.56, M2.61, M2.62, M2.67, M2.68, M2.73, M2.74, M2.79, M2.80, M2.85, M2.86, M2.91, M2.92, M2.97, M2.98, M2.103, M2.104, M2.109, M2.110, M2.115, M2.116, M2.121, M2.122, M2.127, M2.133, M2.134, M2.139, M2.140, M2.145, M2.146, M2.151, M2.152, M2.157, M2.163, M2.164, M2.168, M2.169, M2.170, M2.181, M2.182, M2.187, M2.188, M2.195, M2.196, MPL3115.3 (GND), R4.1, R9.1, R10.1, R13.1, SON_0.4, SON_1.4, SON_2.4, SON_3.4, U1.2 (GND), U2.2 (GND), U3.2 (GND), U5.2 (GND), XT60-MALE.1 (-)
GND1: U$6.MT1 (GND), U$6.MT2 (GND1)
GPS_3DFIX: GPS.P$5 (3D-FIX)
INT1_MPL3115: MPL3115.6 (INT1)
INT2_MPL3115: MPL3115.5 (INT2)
INT_ICM20948: IMU.12 (INT1)
M2_1V8: M2.183, M2.184, M2.185, M2.186
M2_VBAT: M2.197, M2.198, M2.199, M2.200
MISO_M1: M2.29, R1.2, U$6.7 (DATA_OUT)
MOSI_M1: M2.33, R11.2, U$6.3 (DATA_IN)
unnamed: GPS.P$12 (GND), U.FL.P$1 (GND), U.FL.P$2 (GND)
unnamed: GPS.P$11 (EX_ANT), U.FL.P$3 (SIGNAL)
unnamed: R3.1, U1.3 (EN)
unnamed: B1.+$1 (+), B1.+$2 (+), D4.A
unnamed: R2.1, U2.3 (EN)
unnamed: J1.6 (D+), J1.7 (D+), M2.165
unnamed: J1.5 (D-), J1.8 (D-), M2.167
unnamed: M2.39, M2.40
unnamed: C12.1, MPL3115.2 (CAP)
unnamed: R6.1, U5.3 (EN)
unnamed: R5.1, U3.3 (EN)
unnamed: M2.41, M2.42
unnamed: M2.3, R14.2, U$6.2 (CS)
unnamed: D4.C, GPS.P$4 (VBACKUP)
unnamed: C2.1, IMU.10 (REGOUT)
OUT: C1.1, C4.1, C6.1, C10.1, U1.5 (OUT), U2.5 (OUT), U3.5 (OUT), U5.5 (OUT)
RXD1_M1: GPS.P$9 (TX), R7.1
SCK_M1: M2.35, R12.2, U$6.5 (SCLK)
SCL_M1: IMU.23 (SCL/SCLK), MPL3115.7 (SDL)
SDA_M1: IMU.24 (SDA/SDI), MPL3115.8 (SCL)
TRIG_SON0: SON_0.2
TRIG_SON1: SON_1.2
TRIG_SON2: SON_2.2
TRIG_SON3: SON_3.2
TXD1_M1: GPS.P$10 (RX), R8.1
VBUS: J1.2 (VBUS), J1.11 (VBUS)
VCAP/VCORE: U4.56 (VCAP/VCORE)
VDD: U$6.4 (VDD)
VDD1: U4.10 (VDD1)
VDD2: U4.26 (VDD2)
VDD3: U4.38 (VDD3)
VIN: C7.1, C13.1, GPS.P$1 (VCC), IMU.8 (VDDIO), IMU.13 (VDD), IMU.22 (!CS), M2.189, M2.190, M2.191, M2.193, MPL3115.1 (VDD), MPL3115.4 (VDDIO), R1.1, R7.2, R8.2, R11.1, R12.1, R14.1
VSS: U$6.6 (VSS)
VSS1: U4.9 (VSS1)
VSS2: U4.25 (VSS2)
VSS3: U4.41 (VSS3)

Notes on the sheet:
9DoF IMU ICM-20948
Ultrasonic Sensor (HC-SR04)
GPS Module
5V to 3.3V voltage regulator
Altitude Pressure & Temperature Sensor
Raspberry Pi Compute Module 3+
5V to 1.8V voltage regulator
USB_OnTheGo Pin 168 Unused
Powers PHYs, IO and SDRAM
U.FL
Powers PHYs, IO, and SDRAM
5V to 2.8V voltage regulator
Powers composite (TV-out) DAC
Powers GPIO 0-27 pins
Powers GPIO 28-45 pins
Barone 2 Version 1.8

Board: 4 copper layers, 49 parts (0 on the bottom side), 35 nets, no tracks yet.

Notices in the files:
parts and their libraries:
SparkFun-Hardware: Licensing: Creative Commons ShareAlike 4.0 International - https://creativecommons.org/licenses/by-sa/4.0
